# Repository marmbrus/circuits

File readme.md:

# Plugins
- [Fabrication Toolkit](https://github.com/bennymeg/Fabrication-Toolkit)
- [Replicate Layout](https://github.com/MitjaNemec/ReplicateLayout)

# Template Setup
## Preferences -> Configure Paths...
- KICAD_USER_TEMPLATE_DIR=~/workspace/circuits/templates

# Component Setup
## easyeda2kicad
 - [github](https://github.com/uPesy/easyeda2kicad.py)
 - `easyeda2kicad --output ~/workspace/circuits/libraries/easyeda2kicad --full --lcsc_id=...`
## Schematics Editor -> Preferences -> Manage Symbol Libraries...
easyeda2kicad -> circuits/libraries/easyeda2kicad/easyeda2kicad.kicad_sym
## PCB Editor -> Preferences -> Manage Footprint Libraries...
easyeda2kicad -> circuits/libraries/easyeda2kicad/easyeda2kicad.pretty

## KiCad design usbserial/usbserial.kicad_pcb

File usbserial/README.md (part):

# USB Serial Flasher

A USB-C to 3.3 V UART adapter for programming and talking to ESP32 / ESP8266
boards. It uses a WCH CH340C USB-UART bridge, the standard Espressif two-transistor
auto-program circuit (so `esptool` can reset the target into the bootloader on its
own), a jumper-selectable 5 V / 3.3 V supply for the target, and TX/RX activity LEDs.

| | |
|---|---|
| Board | 40.0 × 36.75 mm, 4 layers (In1 = GND plane, In2 = VUSB plane), 1.6 mm |
| Host side | USB-C receptacle, USB 2.0 full speed (12 Mbit/s), bus powered |
| Target side | 6-pin 2.54 mm header: PWR, GND, TXD, RXD, BOOT, RST |
| Logic level | 3.3 V on TXD/RXD (CH340C runs from 3.3 V) |
| Target supply | 5 V (VUSB) or 3.3 V (TPS73733 LDO, 1 A part), or none |
| Baud rate | Up to 2 Mbaud (CH340C); `esptool` at 921600 is fine |
| Revision | v0.2 (see [Revision history](#revision-history)) |

## Block diagram

```mermaid
flowchart LR
    USB[USB-C<br/>USBC201] -- D+/D- --> ESD[USBLC6-2SC6<br/>U401] --> CH[CH340C<br/>U402]
    USB -- VBUS 5 V --> LDO[TPS73733<br/>U101] -- 3.3 V --> CH
    CH -- TXD / RXD<br/>470 Ω --> J101[J101 target header]
    CH -- DTR / RTS --> AP[Q401 / Q402<br/>auto-program] -- RST / BOOT --> J101
    CH -. TX / RX .-> LED[D401 / D402]
    USB -- VUSB --> J102{J102<br/>jumper}
    LDO -- 3.3 V --> J102
    J102 -- PWR --> J101
```

## Connectors

### J101 — target header (1×6, 2.54 mm)

J101 is marked DNP, so JLCPCB does not fit it. Solder a straight or right-angle
header, or wire a cable directly.

| Pin | Name | Direction | Connect to on the target |
|---|---|---|---|
| 1 | PWR | out | 5 V or 3.3 V input, depending on J102 (leave J102 open if the target has its own supply) |
| 2 | GND | — | GND |
| 3 | TXD | out | Target **RX** (U0RXD). CH340C TXD through 470 Ω |
| 4 | RXD | in | Target **TX** (U0TXD). Reaches the CH340C RXD through 470 Ω |
| 5 | BOOT | open collector | GPIO0 / IO0 (or the strapping pin that selects download mode) |
| 6 | RST | open collector | EN / CHIP_PU / RST |

BOOT and RST only ever pull low. The target must provide its own pull-ups
(and the usual RC on EN). Every ESP32 module design already does.

### J102 — target supply select (2×2, 2.54 mm)

Viewed with the USB-C connector at the top, as in the render above:

```
          left    right
  top   [ 3v3 ] [ PWR ]     jumper across the top row    -> PWR = 3.3 V
 bottom [VUSB ] [ PWR ]     jumper across the bottom row -> PWR = 5 V
                            no jumper                    -> PWR not driven
```

> **Never place the jumper vertically on the left column** (VUSB to 3v3).
> That shorts 5 V onto the 3.3 V rail. The CH340C (V3 tied to VCC) would then
> see 5 V, and the LDO output would be driven backwards. See review item R1.

## How the circuit works

### USB-C input — sheet `usb_serial`

* **USBC201** (HRO TYPE-C-31-M-12) is a 16-pin USB 2.0 receptacle. The two D+ and
  two D− contacts are tied together, so the cable works in either orientation.
* **R201 / R202** (5.1 kΩ to GND on CC1/CC2) are the Rd pull-downs that identify
  the board as a sink, so a C-to-C cable delivers VBUS. Without them a USB-C charger
  or laptop leaves VBUS off.
* **U401** (USBLC6-2SC6) is a low-capacitance TVS array that clamps ESD on D+/D− and
  VBUS. It is placed between the connector and the CH340C (flow-through pins 1→6
  and 3→4).
* **Shield.** The four shell tabs are tied to GND (new in v0.2), giving ESD
  striking the shell a direct path to the ground plane.
* **C401 / C402** (100 nF + 10 µF) decouple VBUS at the connector.
  Together with C101 that is 11.1 µF nominal. With 0603 X5R DC-bias derating at 5 V
  the effective value stays under the USB 2.0 10 µF inrush limit.

### 3.3 V regulator — root sheet

* **U101** (TI TPS73733DCQ, SOT-223-6) is a fixed 3.3 V, 1 A LDO fed from VUSB.
  It powers the CH340C and, through J102, optionally the target.
* **R101** (10 kΩ) pulls EN up to VUSB, so the regulator is always on.
* **C104** (10 nF) on NR is the noise-reduction cap for the fixed-output version.
* **C101** (input) and **C102 / C103** (output) are 1 µF ceramics. C102's ground now
  has a direct trace to U101 pin 3 (v0.2).
* **Dissipation.** At 5 V in, every 100 mA drawn from 3.3 V costs about 0.17 W in
  U101. A Wi-Fi-active ESP32 averaging 150–250 mA is about 0.25–0.4 W, which is fine
  for the SOT-223 on this copper. Expect it to get warm during transmit bursts.
  Total current is limited by the host port: 500 mA on a USB 2.0 port without
  negotiation.

### USB-UART bridge

* **U402** (CH340C) has an internal oscillator, so no crystal is needed.
* It runs in its **3.3 V configuration**: VCC (pin 16) and V3 (pin 4) both on the
  3v3 rail, decoupled by C403 and C404. Running it from 3.3 V (since commit
  3f91767) keeps TXD, DTR# and RTS# at 3.3 V for ESP32 pins, which are not
  5 V tolerant.
* Unused pins:
  * CTS#, DSR#, RI#, DCD# and NC pins 7/8 are left open.
  * R232 (pin 15) has an internal pull-down and is left open, now with a no-connect
    flag.
* **R402 / R403** (470 Ω) in series with TXD and RXD limit current when the adapter
  and target disagree. Examples: a target powered while the adapter is not, or two
  outputs fighting. In v0.1 these were 487 Ω; 470 Ω is a JLCPCB basic part.

### Auto-program (reset / boot) circuit

Q401/Q402 (MMBT3904) and R404/R405 (12 kΩ) form Espressif's cross-coupled circuit:

* Q401 pulls **RST** low when DTR# is high and RTS# is low.
* Q402 pulls **BOOT** low when RTS# is high and DTR# is low.
* When both lines are at the same level, nothing is pulled.

That last case means a terminal that asserts or deasserts both lines together will
not reset the target.

| DTR# pin | RTS# pin | RST (EN) | BOOT (IO0) |
|---|---|---|---|
| H | H | released | released |
| L | L | released | released |
| H | L | **low** (reset) | released |
| L | H | released | **low** (download mode) |

`esptool` drives these pins to reset the target (RST low), then releases RST while
holding BOOT low. The chip samples IO0 on the way out of reset and starts the ROM
bootloader. No buttons are needed.

### TX / RX activity LEDs (new in v0.2)

Each LED and its 1 kΩ resistor sit between 3v3 and a UART line, with the cathode on
the line. The LED lights while the line is low, so it flickers with traffic and is
dark when idle (UART idles high).

| LED | Driven by | Tapped at | Why there |
|---|---|---|---|
| D401 TX | CH340C TXD pin | CH340C side of R402 (net `CH340_TXD`) | The CH340C sinks the LED current. The target still sees a clean 470 Ω source. |
| D402 RX | the target's TX pin | connector side of R403 (net `RXD`) | The target sinks the LED current directly. On the other side, its ~1.4 mA would drop across R403 and erode the CH340C's input-low margin. |

* **Current.** (3.3 V − ~1.8 V red Vf − ~0.1 V) / 1 kΩ ≈ 1.4 mA per LED. That is
  plenty for a modern 0603 LED, and trivial for either driver to sink.
* **Parts.** D401/D402 are red KT-0603R (LCSC C2286) and R406/R407 are 1 kΩ
  (C21190). Both are JLCPCB basic parts, and the red LED is the same one used on the
  other boards in this repo. For two colours, the yellow 0603 basic part (C72038)
  has a similar Vf and drops in with no other change. Green and blue 0603 parts have
  a ~2.6–3 V Vf, which leaves too little headroom at 3.3 V.

## Bill of materials

All parts are top-side. Every BOM line carries an LCSC part number; generated
`production/bom.csv` lists the same.

| Ref | Qty | Value | Package | LCSC | MPN | JLC class* |
|---|---|---|---|---|---|---|
| C101 C102 C103 | 3 | 1 µF | 0603 | C15849 | Samsung CL10A105KB8NNNC | Basic |
| C104 | 1 | 10 nF | 0603 | C57112 | Samsung CL10B103KB8NNNC | Basic |
| C401 C403 C404 | 3 | 100 nF | 0603 | C14663 | YAGEO CC0603KRX7R9BB104 | Basic |
| C402 | 1 | 10 µF | 0603 | C19702 | Samsung CL10A106KP8NNNC | Basic |
| R101 | 1 | 10 kΩ | 0603 | C25804 | UNI-ROYAL 0603WAF1002T5E | Basic |
| R201 R202 | 2 | 5.1 kΩ | 0603 | C23186 | UNI-ROYAL 0603WAF5101T5E | Basic |
| R402 R403 | 2 | 470 Ω | 0603 | C23179 | UNI-ROYAL 0603WAF4700T5E | Basic |
| R404 R405 | 2 | 12 kΩ | 0603 | C22790 | UNI-ROYAL 0603WAF1202T5E | Basic |
| R406 R407 | 2 | 1 kΩ | 0603 | C21190 | UNI-ROYAL 0603WAF1001T5E | Basic |
| D401 D402 | 2 | LED red | 0603 | C2286 | Hubei KENTO KT-0603R | Basic |
| Q401 Q402 | 2 | MMBT3904 | SOT-23 | C20526 | CJ MMBT3904 | Basic |
| U101 | 1 | TPS73733 | SOT-223-6 | C5220270 | TI TPS73733DCQR | Extended |
| U401 | 1 | USBLC6-2SC6 | SOT-23-6 | C7519 | ST USBLC6-2SC6 | Extended |
| U402 | 1 | CH340C | SOIC-16 | C84681 | WCH CH340C | Extended |
| USBC201 | 1 | USB-C 16P | SMD | C165948 | HRO TYPE-C-31-M-12 | Extended |
| J102 | 1 | 2×2 header | THT 2.54 mm | C18078211 | — | Extended (THT) |
| J101 | 1 | 1×6 header | THT 2.54 mm | — | DNP | — |

\* Basic/extended status from JLCPCB's catalogue as I know it. JLC's catalogue was
not reachable from the environment these files were prepared in, so confirm stock
and class when you upload the BOM.

## Datasheets

The part data lives in the schematic: every symbol has `LCSC Part`, `MPN`,
`Manufacturer` and (where available) a `Datasheet` URL.

**The PDFs have not been synced into this repo yet.** The cloud session that
prepared v0.2 could not reach any datasheet host: datasheet.lcsc.com, lcsc.com,
ti.com, st.com, onsemi.com, wch-ic.com, jlcpcb.com, DigiKey, Mouser and element14
were all blocked by its network policy. To pull them into `usbserial/datasheets/`
with the [kicad-happy](https://github.com/aklofas/kicad-happy) plugin this repo
enables, run from a machine with normal internet access:

```bash
python3 <kicad-happy>/skills/lcsc/scripts/sync_datasheets_lcsc.py usbserial/usbserial.kicad_sch
```

| Part | Manufacturer | Datasheet |
|---|---|---|
| CH340C | WCH | <https://www.wch-ic.com/downloads/CH340DS1_PDF.html> (LCSC copy: <https://datasheet.lcsc.com/szlcsc/Jiangsu-Qin-Heng-CH340C_C84681.pdf>) |
| TPS73733 | Texas Instruments | <https://www.ti.com/lit/ds/symlink/tps737.pdf> |
| USBLC6-2SC6 | STMicroelectronics | <https://www.st.com/resource/en/datasheet/usblc6-2.pdf> |
| TYPE-C-31-M-12 | HRO | <https://lcsc.com/product-detail/USB-Type-C_Korean-Hroparts-Elec-TYPE-C-31-M-12_C165948.html> |
| MMBT3904 | CJ (onsemi equivalent) | <https://www.lcsc.com/product-detail/C20526.html> |
| KT-0603R | Hubei KENTO | <https://www.lcsc.com/product-detail/C2286.html> |

## Design review (v0.2)

**Method.** I re-ran ERC and DRC (with schematic parity) in KiCad 9.0.9, read the
netlist, and inspected the layout. Pinouts were checked against each part's
published pinout:
* CH340C SOIC-16, pins 1–16
* TPS737 DCQ: IN 1, OUT 2, GND 3/6, NR 4, EN 5
* USBLC6-2SC6 flow-through pinout
* MMBT3904 SOT-23: B 1, E 2, C 3
* the 16-pin USB-C pad map

**These are consistency checks against known pinouts, not a re-read of the PDFs**,
which were unavailable (see above). Re-check U101 and U402 against the PDFs once
they are synced.

| | v0.1 | v0.2 |
|---|---|---|
| ERC errors | 9 | **0** (26 warnings, see R8) |
| DRC errors | 3 | **0** (22 warnings, see R8) |
| Unconnected items / parity issues | 0 / 0 | 0 / 0 |

### Fixed in v0.2

| # | Issue | Fix |
|---|---|---|
| F1 | **USB-C shell (4 tabs) floating.** ESD hitting the shell had no defined return path. | Tied to GND in schematic and PCB. The tabs join the GND pours on F.Cu, B.Cu and In1. |
| F2 | **USB-C locating-peg holes modelled as plated** (0.75 mm hole, 0.75 mm pad, negative annular ring; 2 DRC errors). | Converted to NPTH. |
| F3 | **CPL would place U101 rotated 180°** (details below). | Corrected in `positions.csv`. Added `FT Rotation Offset = -180` to U101 so Fabrication Toolkit reproduces it. |
| F4 | **`production/` was stale** (March 2025). It predated 3f91767, so it described the CH340C still on VUSB, at 5 V. | Regenerated from the v0.2 board. |
| F5 | R402/R403 = 487 Ω, an E96 value that is not a JLC basic part. | 470 Ω (C23179). |
| F6 | U101 GND pin 3 had a starved thermal (1 spoke; DRC error). | Solid connection, plus a direct trace to C102's ground pad. |
| F7 | ERC hygiene: SBU1/SBU2/R232 unflagged, no PWR_FLAG on GND, two dangling wire stubs at Q401/Q402, empty title blocks. | Flags added, stubs removed, title blocks filled in. |
| F8 | Board silk text was 0.10 mm line width, below JLC's 0.15 mm minimum. USB-C silk printed past the board edge. | 0.15 mm; connector silk clipped to the outline. |
| F9 | Most parts had no LCSC number, leaving JLC to guess. | LCSC / MPN / manufacturer fields on every part. |

**F3 details.** Fabrication Toolkit adds 180° to any footprint whose name matches
`^SOT-223`. That is correct for KiCad's own SOT-223, but U101 uses the
easyeda2kicad import `SOT-223-6_…-BR`, which is already in LCSC's native
orientation: pins on the right, pin 1 bottom-right, as the `-BR` suffix says. The
v0.1 CPL put U101 at 0° instead of 180°, which would land the tab on pins 1–5.
`leds/lamp` uses the same footprint and got the same +180°, so check that board's
CPL too.

### Open recommendations (not changed)

These are judgement calls left to you.

| # | Severity | Finding | Suggestion |
|---|---|---|---|
| R1 | Medium | **J102 has one destructive position.** A vertical jumper on the left column shorts VUSB to 3v3. That forces 5 V onto the CH340C (V3 tied to VCC; outside the 3.3 V configuration) and back-drives the LDO. | Swap to a 1×3 header ordered VUSB–PWR–3V3, where every jumper position is safe. It fits in the same spot. |
| R2 | Medium | **No current limit on PWR.** A short on the target, or a wiring mistake on J101, goes straight to the host's VBUS (or loads U101). | Add a ~500 mA PTC fuse between VUSB and J102 pin 1. A 0805/1206 part fits next to C101. |
| R3 | Low | **Back-powering an unpowered target.** TXD idles high (3.3 V through 470 Ω), and the RX LED is referenced to 3v3. Both can push a few mA into an unpowered target's I/O clamp diodes. This is normal for this class of adapter. | Power the target first, or from J102. |
| R4 | Low | **Assembly orientation to confirm** in JLC's placement preview: U101 (tab on the big pad), D401/D402 (cathode toward the top of the board, the TX/RX legend), Q401/Q402, U401 (pin 1), U402 (pin 1). | Rotations follow the Fabrication Toolkit conventions used on the other boards; U101 is the one that changed. |
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
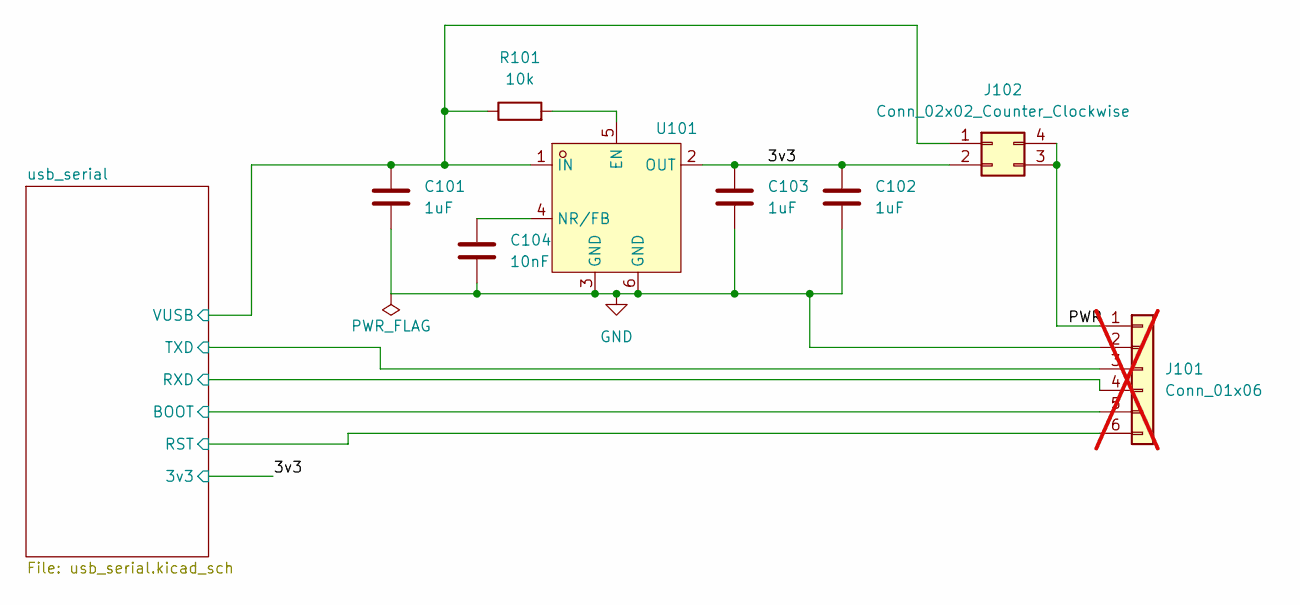
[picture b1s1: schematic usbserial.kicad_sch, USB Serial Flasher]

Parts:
C101, C102, C103: 1uF; C_0603_1608Metric; MPN CL10A105KB8NNNC; LCSC Part C15849
C104: 10nF; C_0603_1608Metric; MPN CL10B103KB8NNNC; LCSC Part C57112
J101: Conn_01x06; PinHeader_1x06_P2.54mm_Vertical; not fitted
J102: Conn_02x02_Counter_Clockwise; PinHeader_2x02_P2.54mm_Vertical; LCSC Part C18078211
R101: 10k; R_0603_1608Metric; MPN 0603WAF1002T5E; LCSC Part C25804
U101: TPS73733DCQ_C5220270; SOT-223-6_L6.5-W3.5-P1.27-LS7.0-BR; MPN TPS73733DCQR; LCSC Part C5220270

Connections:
/3v3: C102.1, C103.1, J102.2, U101.2 (OUT); also elsewhere on the board
/PWR: J101.1, J102.3, J102.4
/usb_serial/BOOT: J101.5; also elsewhere on the board
/usb_serial/RST: J101.6; also elsewhere on the board
/usb_serial/RXD: J101.4; also elsewhere on the board
/usb_serial/TXD: J101.3; also elsewhere on the board
/usb_serial/VUSB: C101.1, J102.1, R101.1, U101.1 (IN); also elsewhere on the board
GND: C101.2, C102.2, C103.2, C104.2, J101.2, U101.3 (GND), U101.6 (GND); also elsewhere on the board
unnamed: R101.2, U101.5 (EN)
unnamed: C104.1, U101.4 (NR/FB)

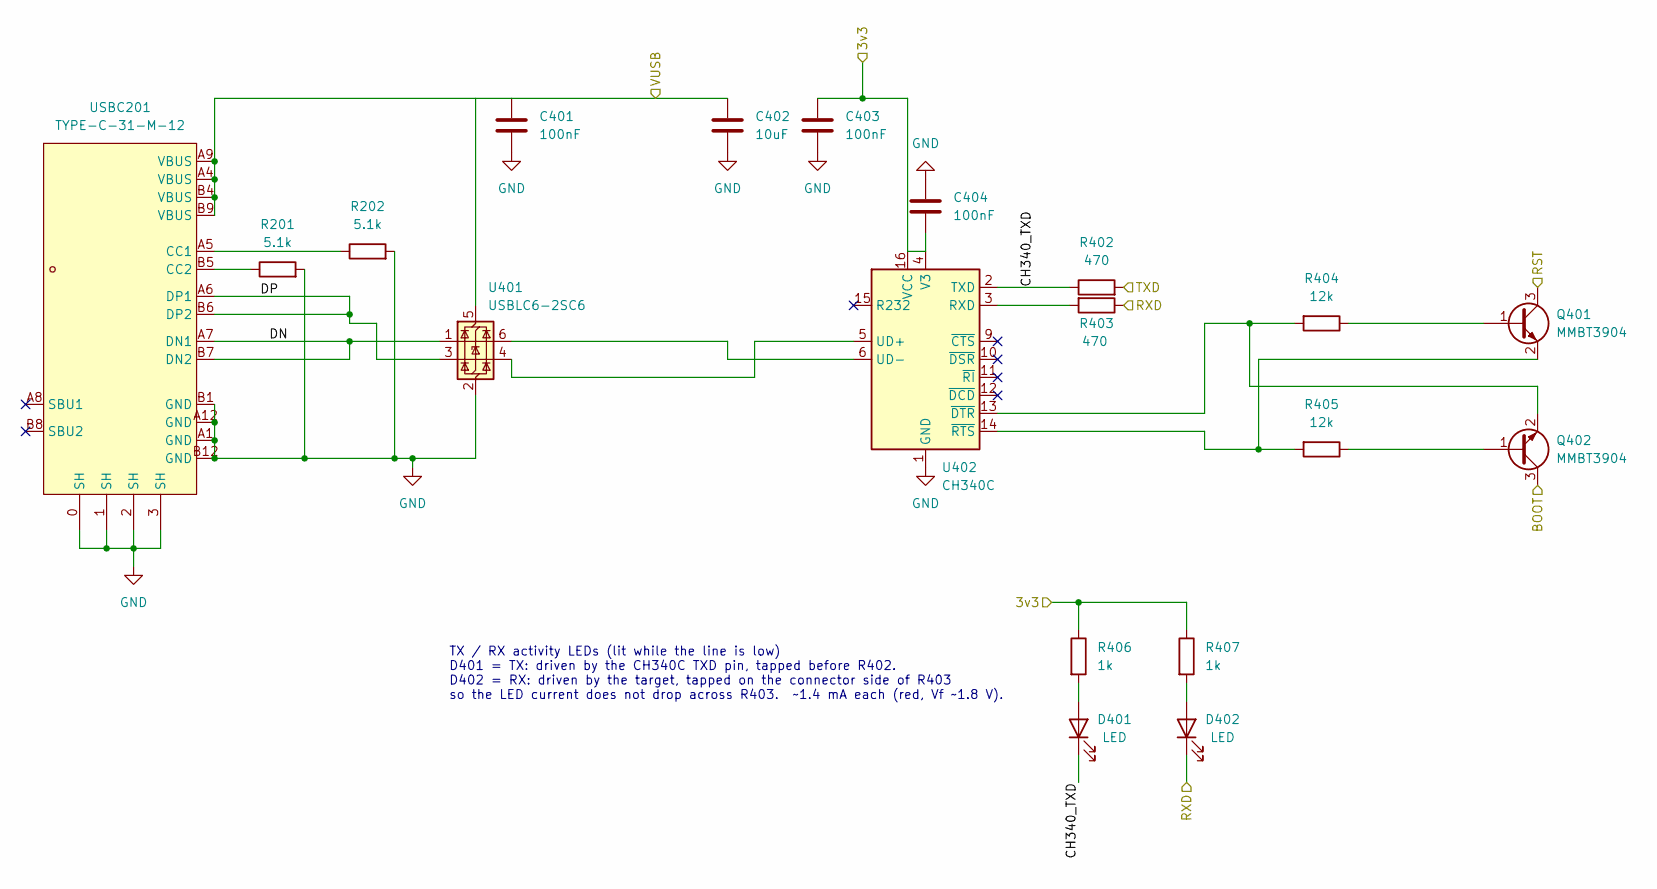
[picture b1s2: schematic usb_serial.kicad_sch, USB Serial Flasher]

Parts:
C401, C403, C404: 100nF; C_0603_1608Metric; MPN CC0603KRX7R9BB104; LCSC Part C14663
C402: 10uF; C_0603_1608Metric; MPN CL10A106KP8NNNC; LCSC Part C19702
D401, D402: LED; LED_0603_1608Metric; MPN KT-0603R; LCSC Part C2286
Q401, Q402: MMBT3904; SOT-23; MPN MMBT3904; LCSC Part C20526
R201, R202: 5.1k; R_0603_1608Metric; MPN 0603WAF5101T5E; LCSC Part C23186
R402, R403: 470; R_0603_1608Metric; MPN 0603WAF4700T5E; LCSC Part C23179
R404, R405: 12k; R_0603_1608Metric; MPN 0603WAF1202T5E; LCSC Part C22790
R406, R407: 1k; R_0603_1608Metric; MPN 0603WAF1001T5E; LCSC Part C21190
U401: USBLC6-2SC6; SOT-23-6; MPN USBLC6-2SC6; LCSC Part C7519
U402: CH340C; SOIC-16_3.9x9.9mm_P1.27mm; MPN CH340C; LCSC Part C84681
USBC201: TYPE-C-31-M-12; USB-C_SMD-TYPE-C-31-M-12; MPN TYPE-C-31-M-12; LCSC Part C165948

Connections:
/3v3: C403.1, C404.2, R406.1, R407.1, U402.4 (V3), U402.16 (VCC); also elsewhere on the board
/usb_serial/BOOT: Q402.3 (C); also elsewhere on the board
/usb_serial/CH340_TXD: D401.1 (K), R402.1, U402.2 (TXD)
/usb_serial/DN: U401.1 (I/O1), USBC201.A7 (DN1), USBC201.B7 (DN2)
/usb_serial/DP: U401.3 (I/O2), USBC201.A6 (DP1), USBC201.B6 (DP2)
/usb_serial/RST: Q401.3 (C); also elsewhere on the board
/usb_serial/RXD: D402.1 (K), R403.1; also elsewhere on the board
/usb_serial/TXD: R402.2; also elsewhere on the board
/usb_serial/VUSB: C401.1, C402.1, U401.5 (VBUS), USBC201.A4 (VBUS), USBC201.A9 (VBUS), USBC201.B4 (VBUS), USBC201.B9 (VBUS); also elsewhere on the board
GND: C401.2, C402.2, C403.2, C404.1, R201.2, R202.2, U401.2 (GND), U402.1 (GND), USBC201.0 (SH), USBC201.1 (SH), USBC201.2 (SH), USBC201.3 (SH), USBC201.A1 (GND), USBC201.A12 (GND), USBC201.B1 (GND), USBC201.B12 (GND); also elsewhere on the board
unnamed: D401.2 (A), R406.2
unnamed: D402.2 (A), R407.2
unnamed: Q401.1 (B), R404.1
unnamed: Q401.2 (E), R405.2, U402.14 (~RTS)
unnamed: Q402.1 (B), R405.1
unnamed: Q402.2 (E), R404.2, U402.13 (~DTR)
unnamed: R403.2, U402.3 (RXD)
unnamed: U401.4 (I/O2), U402.5 (UD+)
unnamed: U401.6 (I/O1), U402.6 (UD-)
unnamed: R202.1, USBC201.A5 (CC1)
unnamed: R201.1, USBC201.B5 (CC2)

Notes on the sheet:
TX / RX activity LEDs (lit while the line is low) D401 = TX: driven by the CH340C TXD pin, tapped before R402. D402 = RX: driven by the target, tapped on the connector side of R403 so the LED current does not drop across R403. ~1.4 mA each (red, Vf ~1.8 V).

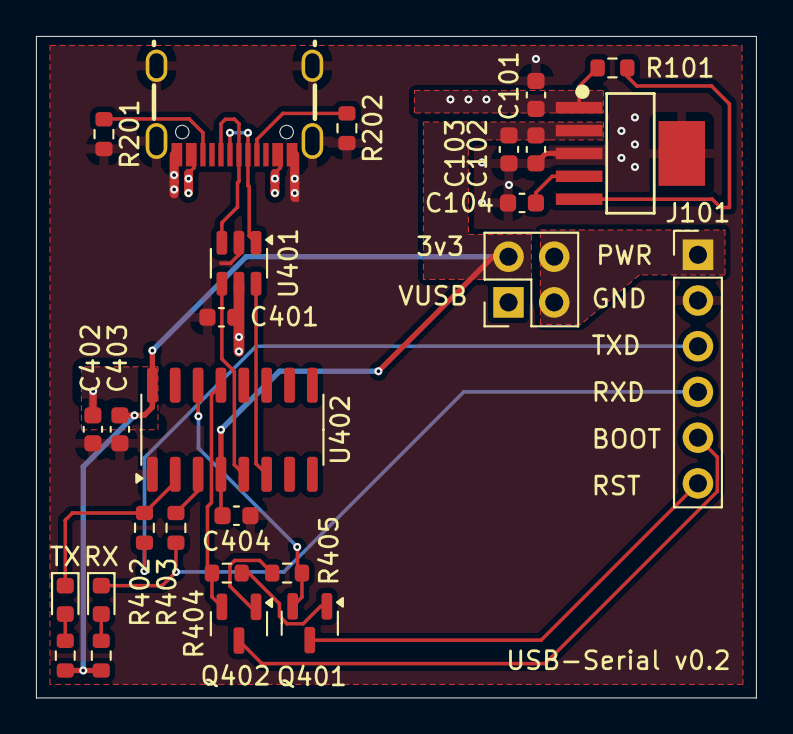
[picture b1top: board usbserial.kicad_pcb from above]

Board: 4 copper layers, 40.0 x 36.8 mm, 27 parts (0 on the bottom side), 24 nets.

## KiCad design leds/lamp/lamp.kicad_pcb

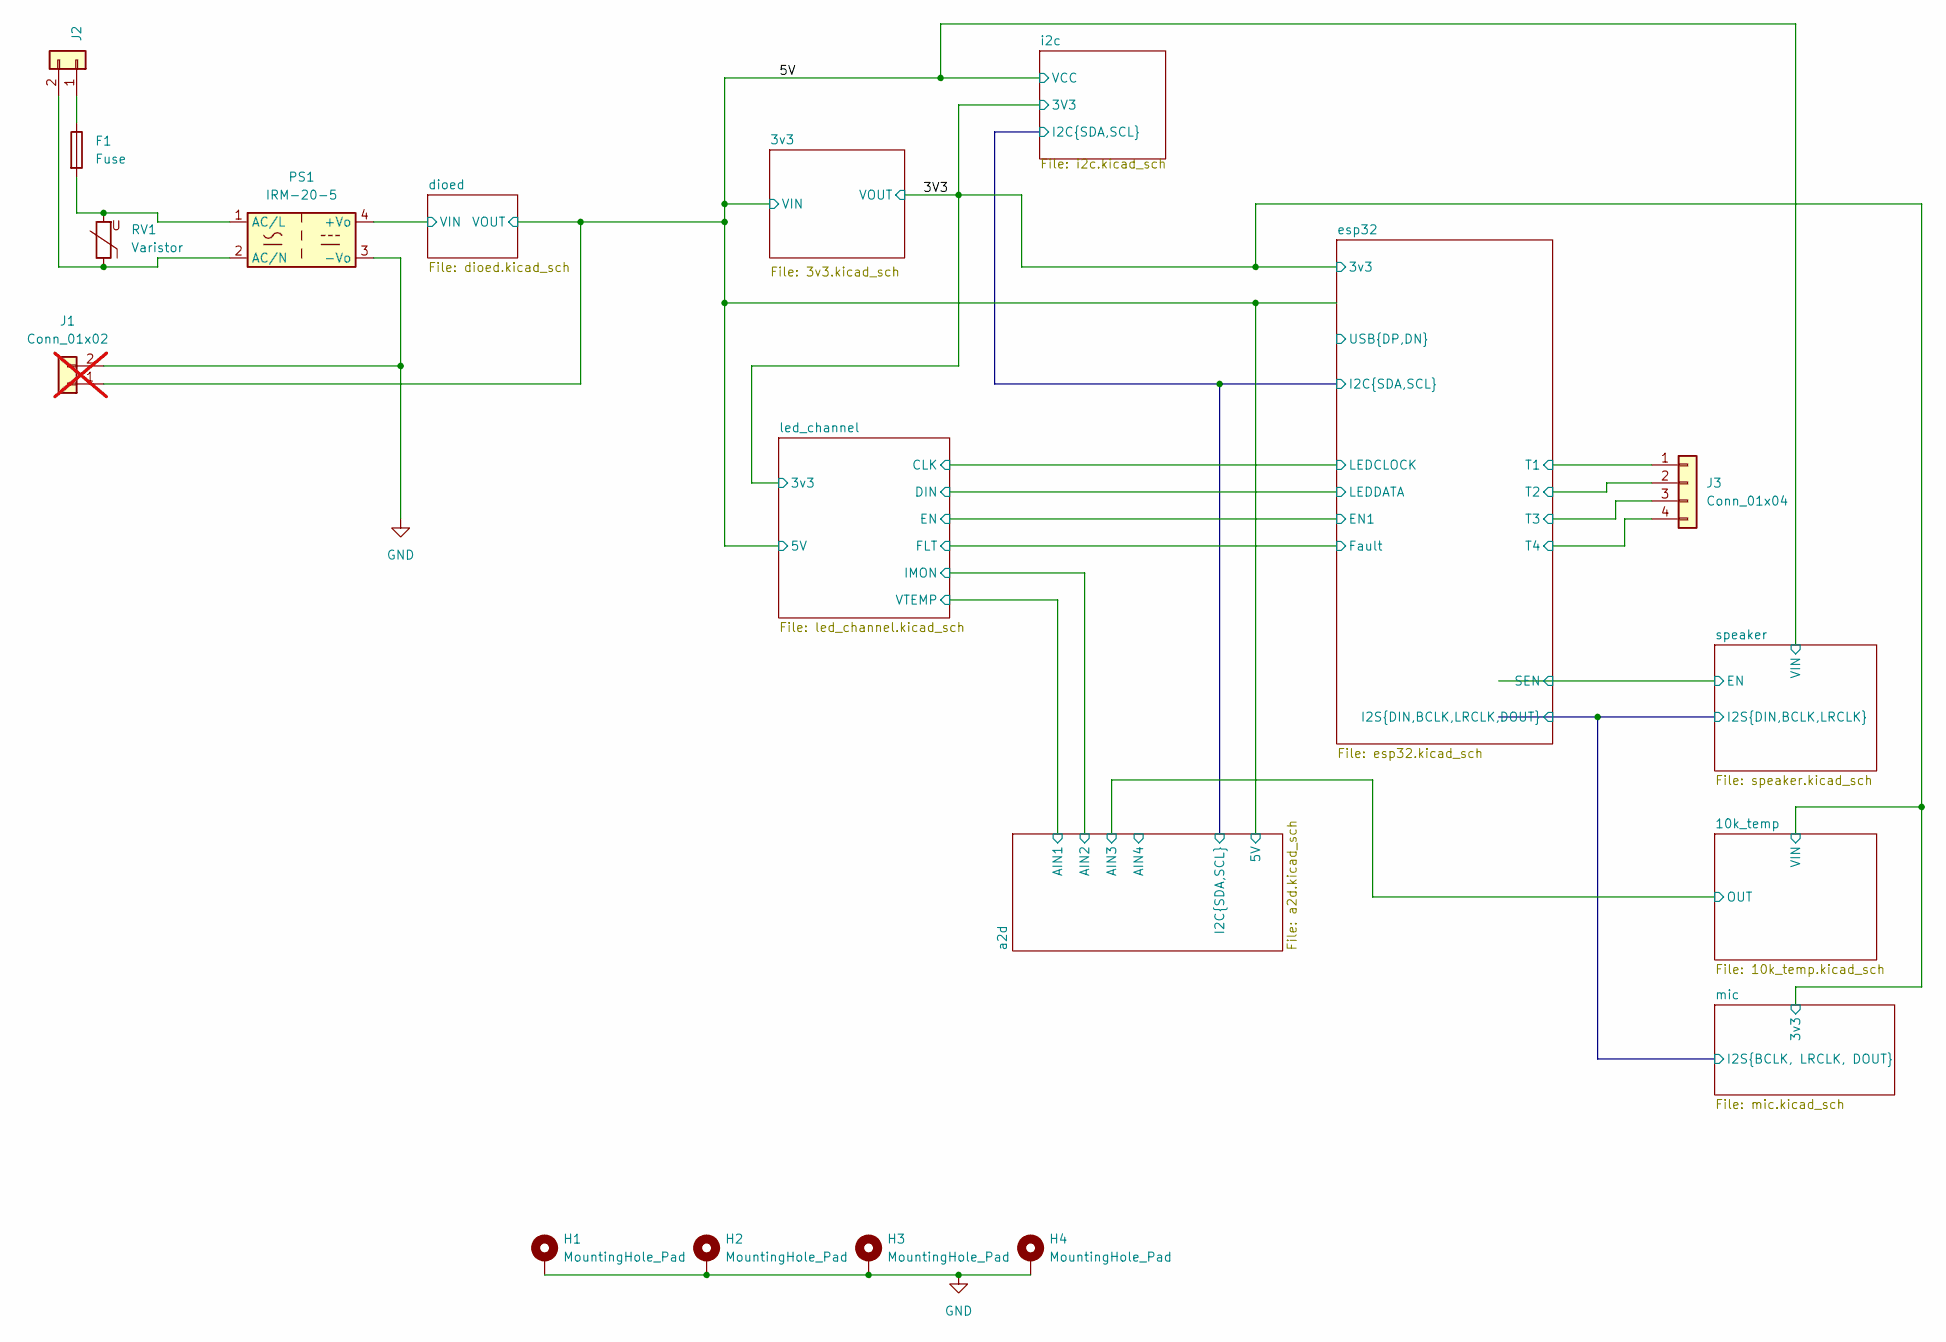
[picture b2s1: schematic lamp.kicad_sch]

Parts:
F1: Fuse; FUSE-SMD_L9.8-W5.0_01550900M; LCSC Part C108518
H1, H2, H3, H4: MountingHole_Pad; MountingHole_3.2mm_M3_Pad_Via
J1: Conn_01x02; Molex_Nano-Fit_105309-xx02_1x02_P2.50mm_Vertical; LCSC Part C2938824; not fitted
J2: Conn_01x02; Molex_Mini-Fit_Jr_5569-02A2_2x01_P4.20mm_Horizontal; LCSC Part C240832
J3: Conn_01x04; Molex_Nano-Fit_105310-xx04_2x02_P2.50mm_Vertical; LCSC Part C5271185
PS1: IRM-20-5; Converter_ACDC_MeanWell_IRM-20-xx_THT
RV1: Varistor; RV_Disc_D12mm_W7.5mm_P7.5mm; LCSC Part C179027

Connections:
/5V: J1.1; also elsewhere on the board
/dioed/VIN: PS1.4 (+Vo); also elsewhere on the board
/esp32/T1: J3.1; also elsewhere on the board
/esp32/T2: J3.2; also elsewhere on the board
/esp32/T3: J3.3; also elsewhere on the board
/esp32/T4: J3.4; also elsewhere on the board
GND: H1.1, H2.1, H3.1, H4.1, J1.2, PS1.3 (-Vo); also elsewhere on the board
unnamed: F1.1, J2.1
unnamed: J2.2, PS1.2 (AC/N), RV1.1
unnamed: F1.2, PS1.1 (AC/L), RV1.2

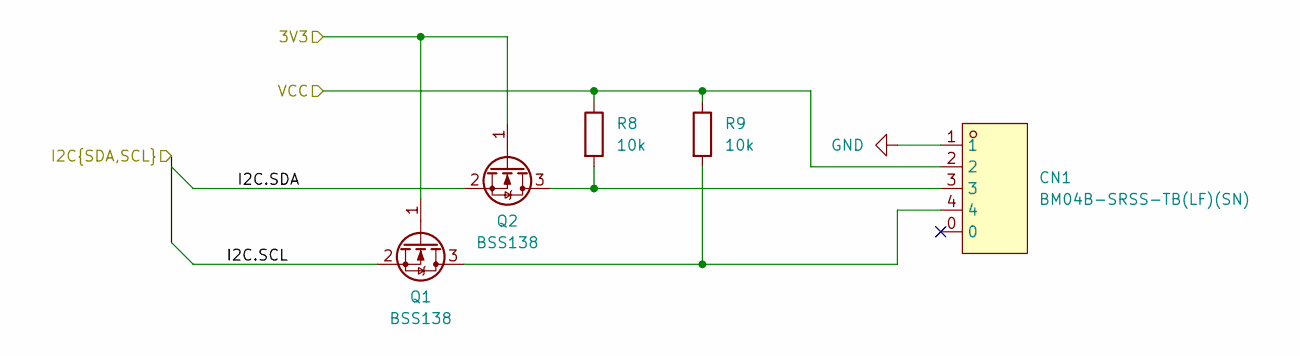
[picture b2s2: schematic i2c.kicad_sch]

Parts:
CN1: BM04B-SRSS-TB(LF)(SN); CONN-SMD_BM04B-SRSS-TB; LCSC Part C160390
Q1, Q2: BSS138; SOT-23
R8, R9: 10k; R_0603_1608Metric

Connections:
/3V3: Q1.1 (G), Q2.1 (G); also elsewhere on the board
/5V: CN1.2, R8.1, R9.1; also elsewhere on the board
/a2d/I2C.SCL: Q1.2 (S); also elsewhere on the board
/a2d/I2C.SDA: Q2.2 (S); also elsewhere on the board
GND: CN1.1; also elsewhere on the board
unnamed: CN1.4, Q1.3 (D), R9.2
unnamed: CN1.3, Q2.3 (D), R8.2

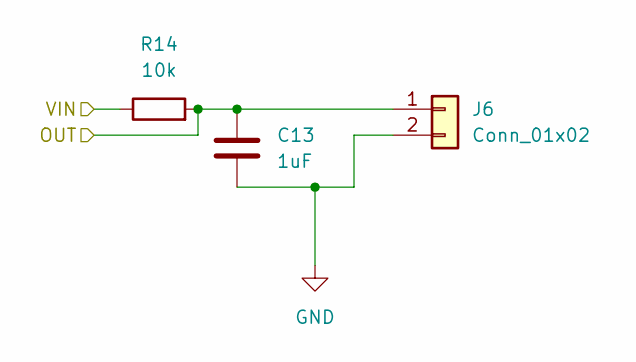
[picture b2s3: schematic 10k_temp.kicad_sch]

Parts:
C13: 1uF; C_0603_1608Metric
J6: Conn_01x02; Molex_Nano-Fit_105309-xx02_1x02_P2.50mm_Vertical; LCSC Part C2938824
R14: 10k; R_0805_2012Metric

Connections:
/3V3: R14.1; also elsewhere on the board
/10k_temp/OUT: C13.1, J6.1, R14.2; also elsewhere on the board
GND: C13.2, J6.2; also elsewhere on the board

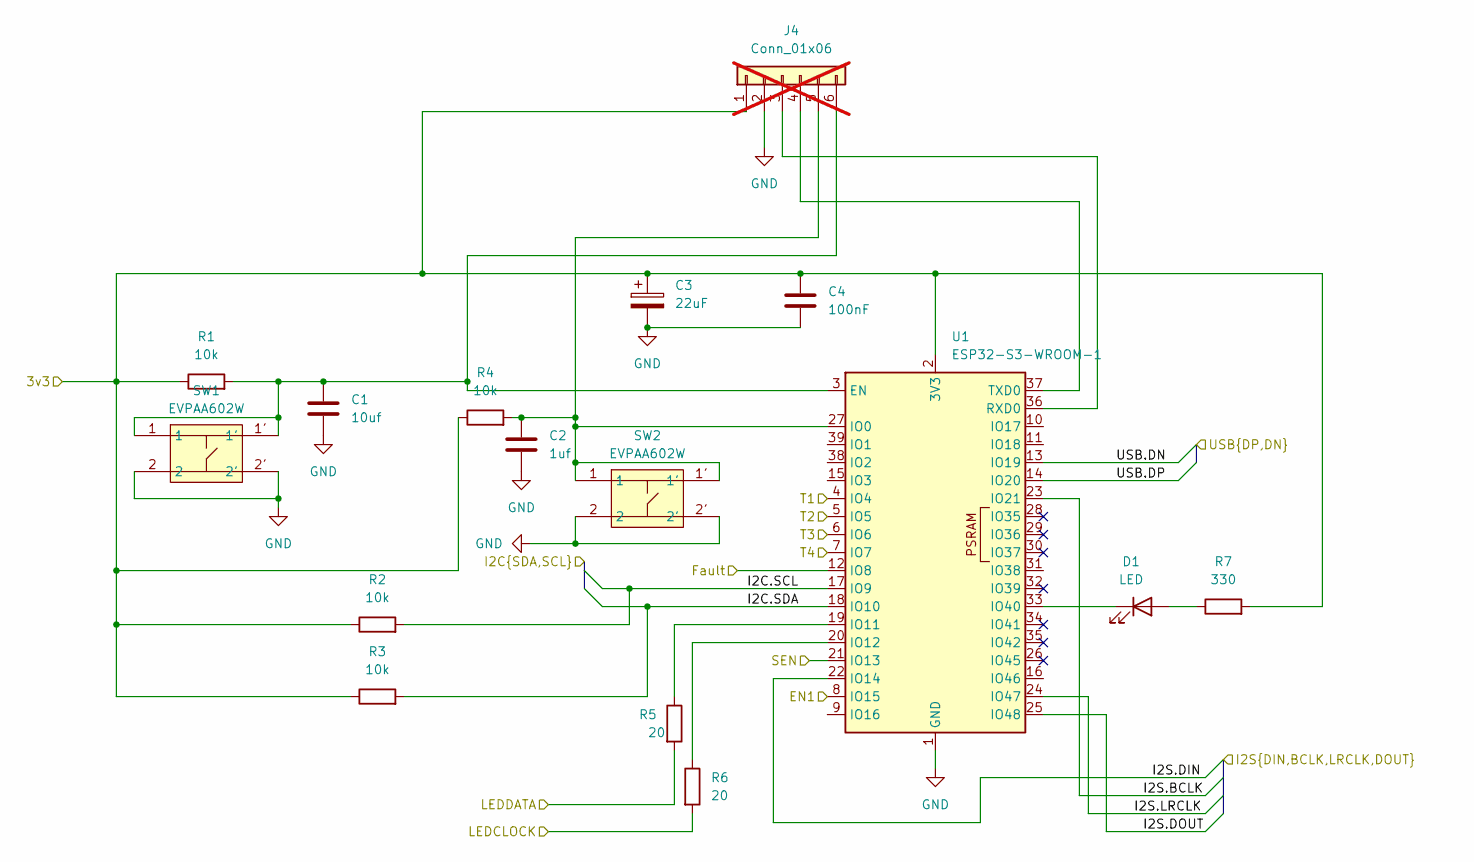
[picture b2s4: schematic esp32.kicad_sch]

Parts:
C1: 10uf; C_0603_1608Metric
C2: 1uf; C_0603_1608Metric
C3: 22uF; C_Elec_5x5.8; LCSC Part C336246
C4: 100nF; C_0603_1608Metric
D1: LED; LED_0603_1608Metric; LCSC Part C2290
J4: Conn_01x06; PinHeader_1x06_P2.54mm_Vertical; not fitted
R1, R2, R3, R4: 10k; R_0603_1608Metric
R5, R6: 20; R_0603_1608Metric
R7: 330; R_0603_1608Metric
SW1, SW2: EVPAA602W; KEY-TH_4P-L3.5-W4.9-P2.80-LS4.3; LCSC Part C79148
U1: ESP32-S3-WROOM-1; LCSC Part C2913202

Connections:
/3V3: C3.1, C4.1, J4.1, R1.1, R2.1, R3.1, R4.1, R7.2, U1.2 (3V3); also elsewhere on the board
/a2d/I2C.SCL: R2.2, U1.17 (IO9); also elsewhere on the board
/a2d/I2C.SDA: R3.2, U1.18 (IO10); also elsewhere on the board
/esp32/EN1: U1.8 (IO15); also elsewhere on the board
/esp32/Fault: U1.12 (IO8); also elsewhere on the board
/esp32/I2S.BCLK: U1.23 (IO21); also elsewhere on the board
/esp32/I2S.DIN: U1.22 (IO14); also elsewhere on the board
/esp32/I2S.DOUT: U1.25 (IO48); also elsewhere on the board
/esp32/I2S.LRCLK: U1.24 (IO47); also elsewhere on the board
/esp32/LEDCLOCK: R6.2; also elsewhere on the board
/esp32/LEDDATA: R5.2; also elsewhere on the board
/esp32/SEN: U1.21 (IO13); also elsewhere on the board
/esp32/T1: U1.4 (IO4); also elsewhere on the board
/esp32/T2: U1.5 (IO5); also elsewhere on the board
/esp32/T3: U1.6 (IO6); also elsewhere on the board
/esp32/T4: U1.7 (IO7); also elsewhere on the board
/esp32/USB.DN: U1.13 (IO19)
/esp32/USB.DP: U1.14 (IO20)
GND: C1.2, C2.2, C3.2, C4.2, J4.2, SW1.2, SW1.2', SW2.2, SW2.2', U1.1 (GND), U1.40 (GND), U1.41 (GND); also elsewhere on the board
unnamed: D1.2 (A), R7.1
unnamed: D1.1 (K), U1.33 (IO40)
unnamed: J4.3, U1.36 (RXD0)
unnamed: J4.4, U1.37 (TXD0)
unnamed: C2.1, J4.5, R4.2, SW2.1, SW2.1', U1.27 (IO0)
unnamed: C1.1, J4.6, R1.2, SW1.1, SW1.1', U1.3 (EN)
unnamed: R5.1, U1.19 (IO11)
unnamed: R6.1, U1.20 (IO12)

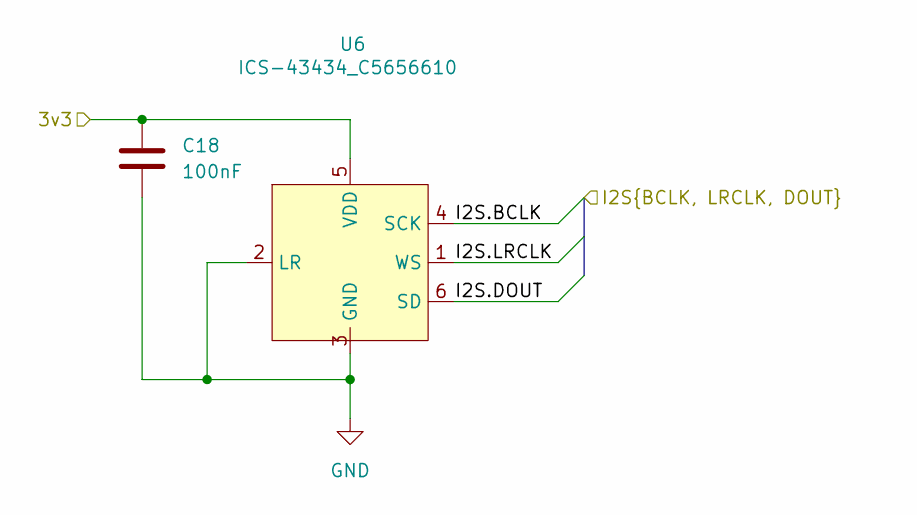
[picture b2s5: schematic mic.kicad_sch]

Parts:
C18: 100nF; C_0603_1608Metric
U6: ICS-43434_C5656610; MIC-SMD_6P-L3.5-W2.7-P0.90-BL; LCSC Part C5656610

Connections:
/3V3: C18.1, U6.5 (VDD); also elsewhere on the board
/esp32/I2S.BCLK: U6.4 (SCK); also elsewhere on the board
/esp32/I2S.DOUT: U6.6 (SD); also elsewhere on the board
/esp32/I2S.LRCLK: U6.1 (WS); also elsewhere on the board
GND: C18.2, U6.2 (LR), U6.3 (GND); also elsewhere on the board

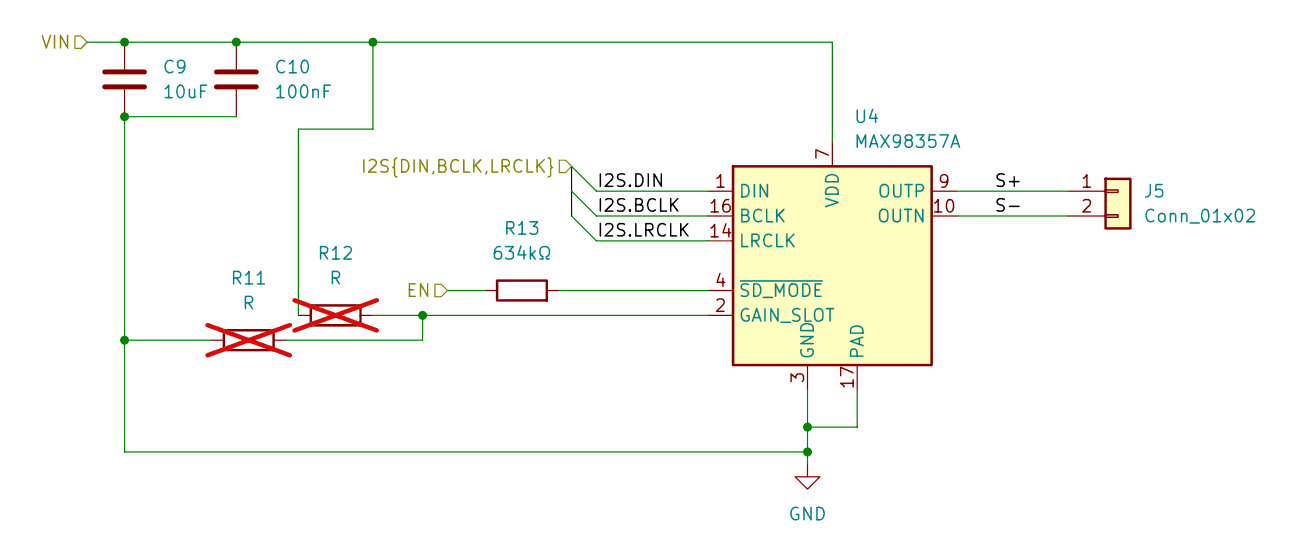
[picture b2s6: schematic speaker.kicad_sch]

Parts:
C9: 10uF; C_0603_1608Metric
C10: 100nF; C_0603_1608Metric
J5: Conn_01x02; Molex_Nano-Fit_105309-xx02_1x02_P2.50mm_Vertical; LCSC Part C2938824
R11, R12: R; R_0805_2012Metric; not fitted
R13: 634kΩ; R_0603_1608Metric
U4: MAX98357A; TQFN-16-1EP_3x3mm_P0.5mm_EP1.23x1.23mm; LCSC Part C910544

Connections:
/5V: C9.1, C10.1, R12.1, U4.7 (VDD), U4.8 (VDD); also elsewhere on the board
/esp32/I2S.BCLK: U4.16 (BCLK); also elsewhere on the board
/esp32/I2S.DIN: U4.1 (DIN); also elsewhere on the board
/esp32/I2S.LRCLK: U4.14 (LRCLK); also elsewhere on the board
/esp32/SEN: R13.1; also elsewhere on the board
/speaker/S+: J5.1, U4.9 (OUTP)
/speaker/S-: J5.2, U4.10 (OUTN)
GND: C9.2, C10.2, R11.1, U4.3 (GND), U4.11 (GND), U4.15 (GND), U4.17 (PAD); also elsewhere on the board
unnamed: R11.2, R12.2, U4.2 (GAIN_SLOT)
unnamed: R13.2, U4.4 (~SD_MODE)

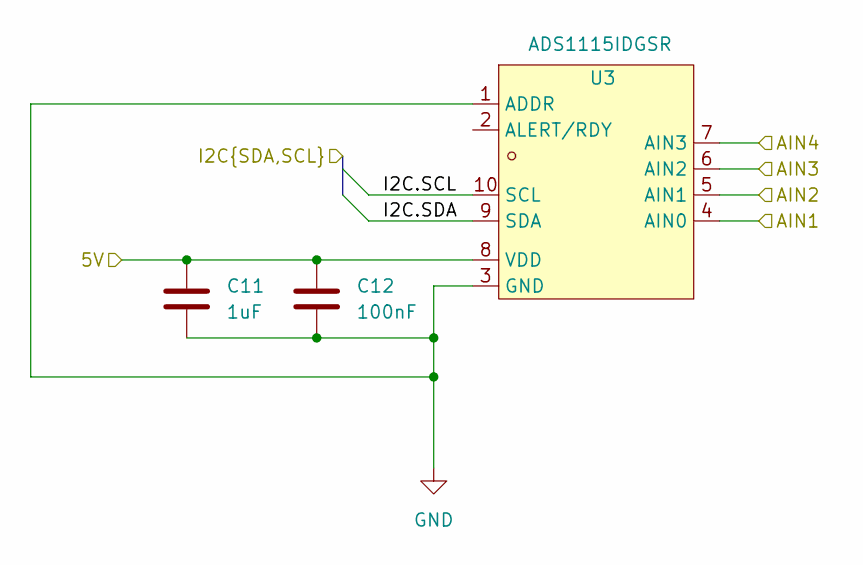
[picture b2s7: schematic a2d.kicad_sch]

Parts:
C11: 1uF; C_0603_1608Metric
C12: 100nF; C_0603_1608Metric
U3: ADS1115IDGSR; MSOP-10_L3.0-W3.0-P0.50-LS5.0-BL; LCSC Part C37593

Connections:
/5V: C11.1, C12.1, U3.8 (VDD); also elsewhere on the board
/10k_temp/OUT: U3.6 (AIN2); also elsewhere on the board
/a2d/AIN1: U3.4 (AIN0); also elsewhere on the board
/a2d/AIN2: U3.5 (AIN1); also elsewhere on the board
/a2d/AIN4: U3.7 (AIN3)
/a2d/I2C.SCL: U3.10 (SCL); also elsewhere on the board
/a2d/I2C.SDA: U3.9 (SDA); also elsewhere on the board
GND: C11.2, C12.2, U3.1 (ADDR), U3.3 (GND); also elsewhere on the board

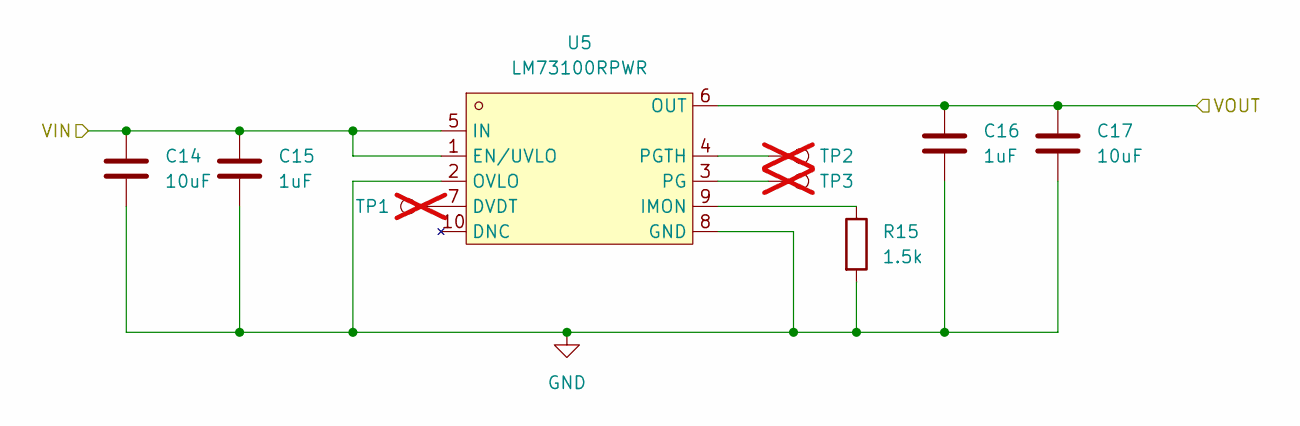
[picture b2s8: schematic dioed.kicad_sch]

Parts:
C14, C17: 10uF; C_0603_1608Metric
C15, C16: 1uF; C_0603_1608Metric
R15: 1.5k; R_0603_1608Metric
TP1, TP2, TP3: TestPoint; TestPoint_Pad_D1.0mm; not fitted
U5: LM73100RPWR; VQFN-10_L2.0-W2.0-P0.45-TL; LCSC Part C3210761

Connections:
/5V: C16.1, C17.1, U5.6 (OUT); also elsewhere on the board
/dioed/VIN: C14.1, C15.1, U5.1 (EN/UVLO), U5.5 (IN); also elsewhere on the board
GND: C14.2, C15.2, C16.2, C17.2, R15.2, U5.2 (OVLO), U5.8 (GND); also elsewhere on the board
unnamed: TP1.1, U5.7 (DVDT)
unnamed: R15.1, U5.9 (IMON)
unnamed: TP3.1, U5.3 (PG)
unnamed: TP2.1, U5.4 (PGTH)

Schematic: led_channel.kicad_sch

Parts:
C19, C23: 100nF; C_0603_1608Metric
C20, C21: 2.2uF; C_0603_1608Metric
C22: 470nF; C_0603_1608Metric
C24: 330uF; CAP-SMD_L7.3-W4.3-FD; LCSC Part C2159214
D2: LED; LED_0603_1608Metric; LCSC Part C2286
J7: Conn_02x05_Top_Bottom; Molex_Nano-Fit_105310-xx10_2x05_P2.50mm_Vertical; LCSC Part C561763
R16: 1k; R_0603_1608Metric
R17, R18: 3.6k; R_0603_1608Metric
R19: 53.6k; R_0603_1608Metric
U7: MP5048AGU-Z; QFN-30_L5.0-W5.0-P0.40-TL_MP5048GU-Z; LCSC Part C22431725

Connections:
/3V3: R16.1; also elsewhere on the board
/5V: U7.1 (VIN), U7.2 (VIN), U7.18 (VIN); also elsewhere on the board
/a2d/AIN1: U7.29 (VTEMP); also elsewhere on the board
/a2d/AIN2: C19.1, R17.1, U7.20 (IMON); also elsewhere on the board
/esp32/EN1: U7.26 (ON); also elsewhere on the board
/esp32/Fault: D2.1 (K), U7.22 (FAULT); also elsewhere on the board
/esp32/LEDCLOCK: J7.6; also elsewhere on the board
/esp32/LEDDATA: J7.1; also elsewhere on the board
/led_channel/VLED: C24.1, J7.2, J7.3, J7.4, J7.5, U7.3 (VOUT), U7.4 (VOUT), U7.5 (VOUT), U7.6 (VOUT), U7.7 (VOUT), U7.8 (VOUT), U7.9 (VOUT), U7.10 (VOUT), U7.11 (VOUT), U7.12 (VOUT), U7.13 (VOUT), U7.14 (VOUT), U7.15 (VOUT), U7.16 (VOUT), U7.17 (VOUT)
GND: C19.2, C20.2, C21.2, C22.2, C23.2, C24.2, J7.7, J7.8, J7.9, J7.10, R17.2, R18.2, R19.2, U7.25 (GND); also elsewhere on the board
unnamed: D2.2 (A), R16.2
unnamed: C20.1, U7.27 (3V)
unnamed: R19.1, U7.24 (CLREF)
unnamed: R18.1, U7.19 (CS)
unnamed: C22.1, U7.21 (SS)
unnamed: C23.1, U7.23 (TIMER)
unnamed: C21.1, U7.28 (VCC)

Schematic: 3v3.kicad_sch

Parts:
C5, C7, C8: 1uF; C_0603_1608Metric
C6: 10nF; C_0603_1608Metric
R10: 10k; R_0603_1608Metric
U2: TPS73733DCQ_C5220270; SOT-223-6_L6.5-W3.5-P1.27-LS7.0-BR; LCSC Part C5220270

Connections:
/3V3: C7.1, C8.1, U2.2 (OUT); also elsewhere on the board
/5V: C5.1, R10.1, U2.1 (IN); also elsewhere on the board
GND: C5.2, C6.2, C7.2, C8.2, U2.3 (GND), U2.6 (GND); also elsewhere on the board
unnamed: R10.2, U2.5 (EN)
unnamed: C6.1, U2.4 (NR/FB)

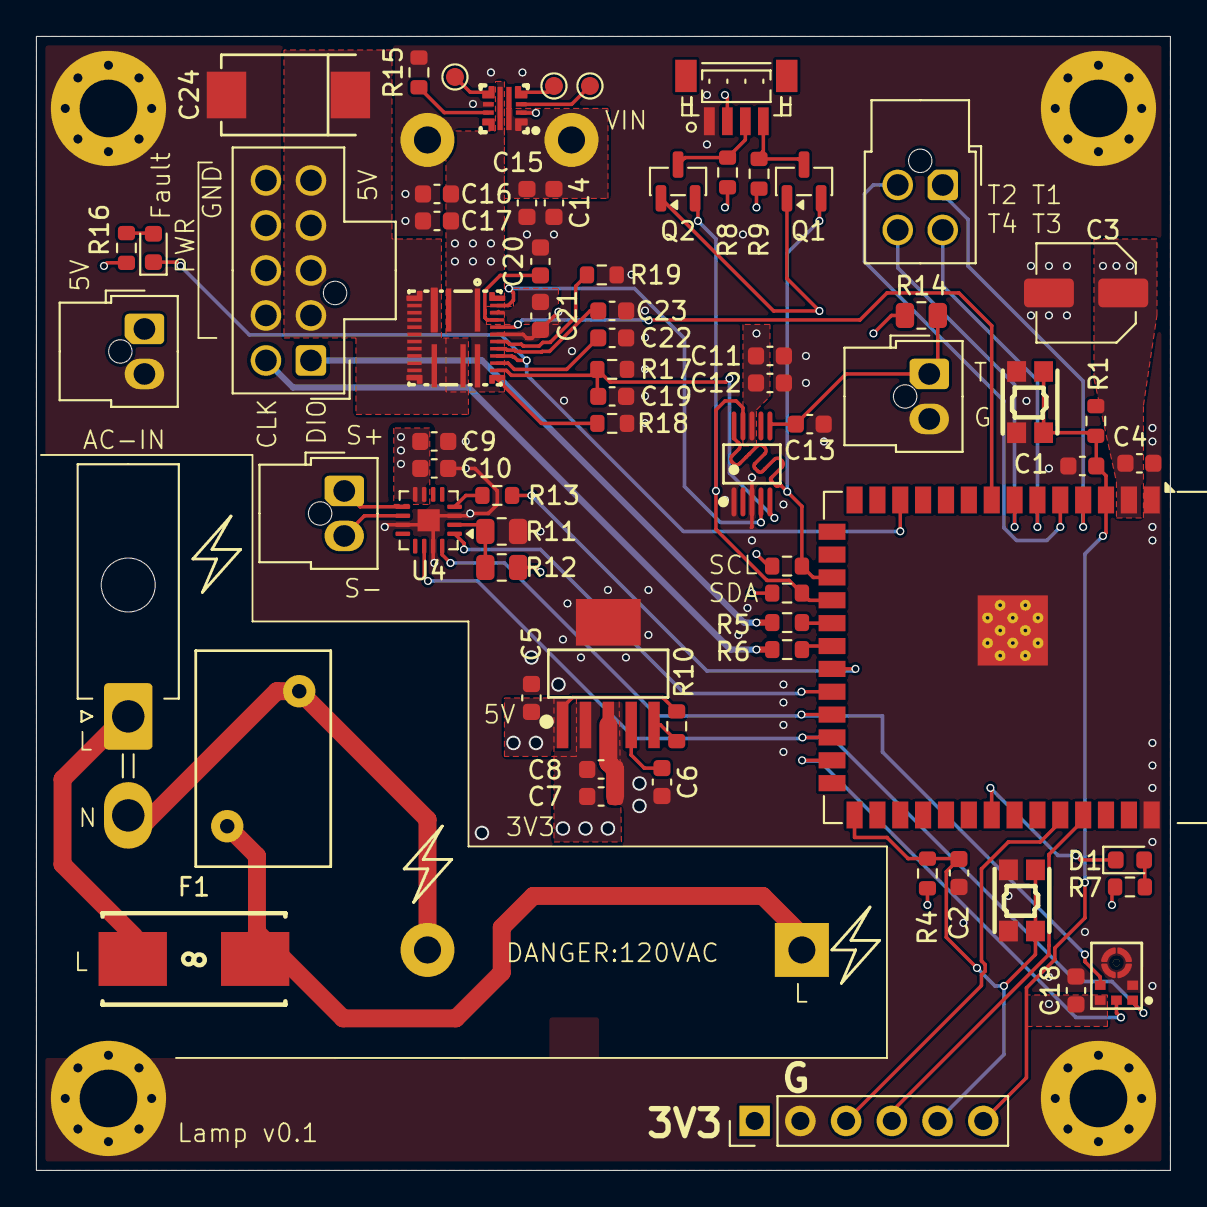
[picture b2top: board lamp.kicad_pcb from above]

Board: 4 copper layers, 63.0 x 63.0 mm, 74 parts (1 on the bottom side), 53 nets.

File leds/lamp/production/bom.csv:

Designator,Footprint,Quantity,Value,LCSC Part #
"C1, C14, C17, C9",0603,4,10uf,
"C10, C12, C18, C19, C23, C4",0603,6,100nF,
"C11, C13, C15, C16, C2, C5, C7, C8",0603,8,1uF,
"C20, C21",0603,2,2.2uF,
C22,0603,1,470nF,
C24,CAP-SMD_L7.3-W4.3-FD,1,330uF,C2159214
C3,C_Elec_5x5.8,1,22uF,C336246
C6,0603,1,10nF,
CN1,CONN-SMD_BM04B-SRSS-TB,1,BM04B-SRSS-TB(LF)(SN),C160390
D1,0603,1,LED,C2290
D2,0603,1,LED,C2286
F1,FUSE-SMD_L9.8-W5.0_01550900M,1,Fuse,C108518
J2,Molex_Mini-Fit_Jr_5569-02A2_2x01_P4.20mm_Horizontal,1,Conn_01x02,C240832
J3,Molex_Nano-Fit_105310-xx04_2x02_P2.50mm_Vertical,1,Conn_01x04,C5271185
"J5, J6",Molex_Nano-Fit_105309-xx02_1x02_P2.50mm_Vertical,2,Conn_01x02,C2938824
J7,Molex_Nano-Fit_105310-xx10_2x05_P2.50mm_Vertical,1,Conn_02x05_Top_Bottom,C561763
PS1,Converter_ACDC_MeanWell_IRM-20-xx_THT,1,IRM-20-5,
"Q1, Q2",SOT-23,2,BSS138,
"R1, R10, R2, R3, R4, R8, R9",0603,7,10k,
R13,0603,1,634kΩ,
R14,0805,1,10k,
R15,0603,1,1.5k,
R16,0603,1,1k,
"R17, R18",0603,2,3.6k,
R19,0603,1,53.6k,
"R5, R6",0603,2,20,
R7,0603,1,330,
RV1,RV_Disc_D12mm_W7.5mm_P7.5mm,1,Varistor,C179027
"SW1, SW2",KEY-TH_4P-L3.5-W4.9-P2.80-LS4.3,2,EVPAA602W,C79148
U1,ESP32-S3-WROOM-1,1,ESP32-S3-WROOM-1,C2913202
U2,SOT-223-6_L6.5-W3.5-P1.27-LS7.0-BR,1,TPS73733DCQ_C5220270,C5220270
U3,MSOP-10_L3.0-W3.0-P0.50-LS5.0-BL,1,ADS1115IDGSR,C37593
U4,TQFN-16-1EP_3x3mm_P0.5mm_EP1.23x1.23mm,1,MAX98357A,C910544
U5,VQFN-10_L2.0-W2.0-P0.45-TL,1,LM73100RPWR,C3210761
U6,MIC-SMD_6P-L3.5-W2.7-P0.90-BL,1,ICS-43434_C5656610,C5656610
U7,QFN-30_L5.0-W5.0-P0.40-TL_MP5048GU-Z,1,MP5048AGU-Z,C22431725
